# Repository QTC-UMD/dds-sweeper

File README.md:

# dds-sweeper

Raspberry Pi Pico interface for the AD9959 DDS.

If you use this project, please cite as:

E. Huegler, J. C. Hill, and D. H. Meyer, An agile radio-frequency source using internal sweeps of a direct digital synthesizer,
*Review of Scientific Instruments*, **94**, 094705 (2023)
[https://doi.org/10.1063/5.0163342](https://doi.org/10.1063/5.0163342)

## Specs

- The timing capabilities of the DDS-Sweeper are tied to the number of clock cycles the pico takes to send the next instruction.  

| Table Mode      | 1 Channel | 2 Channel | 3 Channel | 4 Channel |
|-----------------|-----------|-----------|-----------|-----------|
| Single Stepping | 500       | 750       | 1000      | 1250      |
| Sweep Mode      | 1000      | 1500      | 2000      | 2500      |

- At the default Pico Clock frequency of 125 MHz those clock cycle counts correspond to the following times:  

| Table Mode      | 1 Channel | 2 Channel  | 3 Channel  | 4 Channel  |
|-----------------|-----------|------------|------------|------------|
| Single Stepping | 4 $\mu s$ | 6  $\mu s$ | 8  $\mu s$ | 10 $\mu s$ |
| Sweep Mode      | 8 $\mu s$ | 12 $\mu s$ | 16 $\mu s$ | 20 $\mu s$ |

- The number of instructions you can store in the table depends on the type of sweep being performed, the number of channels being used, and the pico chip version. We allocated a maximum ram size of:

244 kB (RP 2040):

| Table Mode                  | 1 Channel | 2 Channel | 3 Channel | 4 Channel |
|-----------------------------|-----------|-----------|-----------|-----------|
| Single Stepping (Ext Timer) | 16656     | 8615      | 5810      | 4383      |
| Sweep Mode (Ext Timer)      | 8614      | 4382      | 2938      | 2210      |
| Single Stepping (Int Timer) | 5000      | 5000      | 5000      | 4032      |
| Sweep Mode (Int Timer)      | 5000      | 4032      | 2703      | 2033      |

500 kB (RP 2350):

| Table Mode                  | 1 Channel | 2 Channel | 3 Channel | 4 Channel |
|-----------------------------|-----------|-----------|-----------|-----------|
| Single Stepping (Ext Timer) | 34132     | 17654     | 11905     | 8981      |
| Sweep Mode (Ext Timer)      | 17654     | 8981      | 6022      | 4529      |
| Single Stepping (Int Timer) | 5000      | 5000      | 5000      | 5000      |
| Sweep Mode (Int Timer)      | 5000      | 5000      | 5000      | 4353      |

## How to flash the firmware

Download the latest [dds-sweeper.uf2 file](https://github.com/QTC-UMD/dds-sweeper/releases/latest/download/dds-sweeper.uf2).
On your Raspberry Pi Pico, hold down the "bootsel" button while plugging the Pico into USB port on a PC (that must already be turned on).
The Pico should mount as a mass storage device (if it doesn't, try again or consult the Pico documentation).
Drag and drop the `.uf2` file into the mounted mass storage device.
The mass storage device should unmount after the copy completes. Your Pico is now running the DDS Sweeper firmware!

## Usage

### Setup

When the DDS Sweeper is started, configuration is required before it can be used. It is often good to begin with a `reset` command, which resets the AD9959.

First, the clock should be setup with the `setclock` command, followed by the `setmult` command.

Second, the number of channels should be configured with the `setchannels` command.

Finally, the mode and timing should be setup with the `mode` command. The DDS Sweeper uses either discrete amplitude, frequency, and phase steps or sweeps of one parameter (possibly with steps of the other parameter) as its primitive instructions. The DDS Sweeper can then use internal timing (in which case it generates triggers internally after each step or sweep) or external timing (in which case it waits for external triggers).

### Program loading

Once setup is complete, instructions (steps or sweeps, depending on the mode) and timings can be loaded using the `set`, `seti`, or `setb` commands. In addition to output instructions, there are special stop and repeat instructions (which can only be loaded using `seti` and `setb`). With instructions are loaded, the address (order in which they are executed) is specified, so the order of loading need not match the order of execution. Timing is set per address, so it is common to all channels. The stop instruction ends program execution, while the repeat instruction restarts program execution from the beginning. Instructions are loaded into an uninitialized array, so skipping instruction addresses or failing to specify stop/repeat at the end of the program may result in undefined behavior.

### Execution

Finally, the program can be executed using the `start` or `hwstart` commands. If termination of the program is required before it reaches a `stop` command, the `abort` command can be used.

## DDS Units

- Output Amplitude is dependent on frequency (some people on Analog Devices forum mentioned amplitude and frequency are related by a sinc function)

- The frequency resolution of the AD9959 is $= \frac{f_{sys clk}}{2^{32}}$. At the default system clock of 500 MHz, the frequency resolution is $\approx 0.1164$ Hz. Frequency input to the DDS Sweeper using the `set` command will be rounded to an integer multiple of the frequency resolution. Frequency input to the DDS Sweeper using the `seti` or `setb` commands will be in units of the frequency resolution.

- The phase resolution of the AD9959 is $= \frac{360^\circ}{2^{14}} \approx 0.02197^\circ$. Phase offsets given using the `set` command will be rounded to a multiple of this resolution. Phase offsets given using the `seti` or `setb` commands will be in units of this resolution.

- The amplitude resolution of the AD9959 is $= \frac{1}{2^{10}} \approx 0.09767\%$. Amplitude scale factors given using the `set` command will be rounded to a multiple of this resolution. Amplitude scale factors given using the `seti` or `setb` commands will be in units of this resolution.

- When the DDS Sweeper uses internal timing to execute instructions, that time is based on the number of clock cycles of the Pico's system clock (which defaults to 125 MHz for an 8 ns period). Timing inputs using the `set` command are given in seconds and will be rounded to an integer multiple of the Pico system clock period. Timing input using the `seti` or `setb` commands is defined to be in units of the Pico system clock period.

## Sweeps

- Setting up a sweep:  
  
Sweeps are defined by two parameters, sweep delta and ramp rate.
- Sweep Delta defines the change in output amplitude/frequency/phase on each sweep step
- Ramp rate defines how often a sweep step is taken. It is based off of the AD9959's sync clock signal which will be one quarter of the AD9959's system clock. The ramp rate parameter specifies the number of sync clock cycles per sweep step. A ramp rate of 1 will cause the sweep delta to be applied every 1 sync clock cycle. For upward sweeps, the ramp rate parameter can have a value of 1-255. For downward sweeps the ramp rate can only be 1.  

For more details on sweeps, see [sweep details](SWEEP_DETAILS.md).

## Serial API

Note: Commands must be terminated with `\n`.

### Status commands

- `version`:  
Responds with a string containing the firmware version.

- `status`:  
Returns the operating status of the DDS-Sweeper.

  - `0`: manual mode
  - `1`: transitioning to buffered execution
  - `2`: buffered execution
  - `3`: aborting buffered execution
  - `4`: last buffered execution was aborted
  - `5`: transitioning to manual mode

- `clkstatus`:
Returns the clocking status of the DDS-Sweeper as three numbers: `<int:mode> <double:freq> <int:mult>`.
Mode can be `0` for internal clocking or `1` for external clocking of the AD9959.
The frequency is the AD9959 reference frequency, in Hz.
`mult` is the AD9959 PLL multiplier. The corresponding system frequency is `freq*-*mult`.

- `board`:
Responds with which type of board the firmware is running on: `pico1` or `pico2`.

- `getfreqs`:  
Responds with a multi-line string containing the current operating frequencies of various clocks (you will be most interested in `pll_sys` and `clk_sys`). Multiline string ends with `ok\n`.

### State commands

- `start`:  
Starts buffered execution immediately.

- `hwstart`:  
Starts buffered execution once an external trigger is received.

- `abort`:  
Stops buffered execution immediately.

### Setup commands

- `setclock <mode:int> <freq:int> (<pll_mult:int>)`:  
Reconfigures the source/reference clock.
  - Mode `0`: Use pico system clock as reference to the AD9959.
    In this mode, the frequency provided also sets the pico system clock
    and it cannot exceed 133 MHz.
    The dds sweeper defaults to this mode with a frequency of 125 MHz and a PLL multiplier of 4.
  - Mode `1`: Sets the AD9959 to receive a reference clock not from the pico.
    Setting this mode does not change the pico system clock.

  `pll_mult` is an optional input that sets the AD9959's PLL multiplier on the Reference Clock input. The default value is 4, giving the AD9959 a system clock of 500 MHz with the pico's 125 MHz reference. Valid values are 1 or 4-20.  
  The AD9959's PLL has an output range of 100-160 MHz or 255-500 MHz with VCO gain enabled. The pico will automatically enable the VCO gain bit if the requested frequency is in the upper range. If trying to use the PLL multiplier to generate a frequency between 160 and 255 MHz, there is no guarantee of operation.

- `setchannels <num:int>`:  
Sets how many channels being used by the table mode. Uses the lowest channels first, starting with channel 0. If number of channels is set to `0`, buffered execution instructions will be written to all 4 channels simultaneously.

- `mode <sweep-type:int> <trigger-source:int>`:  
Configures what mode the DDS-Sweeper is operating in
  - 0: single stepping / manual mode
  - 1: amplitude sweep
  - 2: frequency sweep
  - 3: phase sweep
  - 4: amplitude sweep with frequency/phase steps
  - 5: frequency sweep with amplitude/phase steps
  - 6: phase sweep with frequency/amplitude steps  

  The operating mode must be set before buffered execution instructions can be programmed into the DDS-Sweeper.  
  A `trigger-source` of `0` means the Sweeper is expecting external triggers. A `trigger-source` of `1` means the Sweeper will send its own triggers and `set` commands will require an additional `time` argument.

### Manual output commands

- `setfreq <channel:int> <frequency:float>`:  
Manually set the output frequency of a specified channel. Channels are 0-3 and frequencies are in Hz. If `debug` is set to on, it will respond with the actual frequency set. The Sweeper must be in manual mode.

- `setphase <channel:int> <phase_offset:float>`:  
Manually set the phase offset of a specified channel. Channels are 0-3 and offsets are in degrees. If `debug` is set to on, it will respond with the actual degree offset set. The Sweeper must be in manual mode.

- `setamp <channel:int> <amplitude_scale_factor:float>`:  
Manually set the amplitude scale factor of a specified channel. Channels are 0-3 and amplitude scale factors are a precentage of the maximum output voltage. If `debug` is set to on, it will respond with the actual frequency set. The Sweeper must be in manual mode.

### Data loading commands

- `set`:  
Sets the value of instruction number `addr` for channel `channel` (zero indexed). `addr` starts at 0. It looks different depending on what mode the sweeper is in. If `Debug` is set to `on` it will respond with the actual values set for that instruction.
  - Single Stepping (mode 0): `set <channel:int> <addr:int> <frequency:float> <amplitude:float> <phase:float> (<time:float>)`
  - Sweep Mode (modes 1-3): `set <channel:int> <addr:int> <start_point:float> <end_point:float> <sweep_rate:float> (<time:float>)`

    `start_point` is the value the sweep should start from, and `end_point` is where it will stop. `sweep_rate` is the amount that the output should change in each quantity's units per second (further info below). In the AD9959, the sweep clock runs at one quarter the system clock. The types of values expected for `start_point`, `end_point`, and `sweep_rate` are different depending on the type of sweep:  
    - Amplitude Sweeps (mode 1)  
      `start_point` and `end_point` should be decimals between 0 and 1 that represent the desired proportion of the maximum output amplitude. `sweep_rate` is then that proportion per second. The resolution of the start and end values is $\frac{1}{1024} \approx 0.09766$.
    - Frequency Sweeps (mode 2)  
      `start_point` and `end_point` are frequencies in Hz, with `sweep_rate` in Hz per second. The start and end points can have decimal values, but they will be rounded to the nearest multiple of the frequency resolution ($\frac{f_{sysclk}}{2^{32}}$).
    - Phase Sweeps (mode 3)
      `start_point`, `end_point` are in degrees, with `sweep_rate` in degrees per second. The start and end points can have decimal values, but they will be rounded to the nearest multiple of the phase resolution ($\frac{360^\circ}{2^{14}} \approx 0.02197^\circ$).

  - Sweep and Single Stepping Mode (modes 4-6): `set <channel:int> <addr:int> <start_point:float> <end_point:float> <sweep_rate:float> <secondary1:double> <secondary2:double> (<time:float>)`

  These modes perform a linear sweep on one of the parameters, while simultaneously single stepping on the other two parameters.
  - Amplitude Sweeps (mode 4)  
    `secondary1` is the frequency, and `secondary2` is the phase offset.
  - Frequency Sweeps (mode 5)  
    `secondary1` is the amplitude scale factor, and `secondary2` is the phase offset.
  - Phase Sweeps (mode 6)  
    `secondary1` is the frequency, and `secondary2` is the amplitude scale factor.

- `seti`:  
Sets the value of instruction number `addr` for channel `channel` (zero indexed). `addr` starts at 0. It looks different depending on what mode the sweeper is in. If `Debug` is set to `on` it will respond with the actual values set for that instruction. `seti` uses integer values (AD9959 units) rather than floating point values. Otherwise, it is the same as `set`.
  - Single Stepping (mode 0): `seti <channel:int> <addr:int> <frequency:int> <amplitude:int> <phase:int> (<time:int>)`
  - Sweep Mode (modes 1-3): `seti <channel:int> <addr:int> <start_point:int> <end_point:int> <delta:int> <ramp-rate:int> (<time:int>)`

    `start_point` is the value the sweep should start from, and `end_point` is where it will stop. `delta` is the amount that the output should change by every cycle of the sweep clock. In the AD9959, the sweep clock runs at one quarter the system clock. `ramp-rate` is an additional divider that can applied to slow down the sweep clock further, must be in the range 1-255. The types of values expected for `start_point`, `end_point`, and `delta` different depending on the type of sweep  
    - Amplitude Sweeps (mode 1)  
      `start_point` and `end_point` should be integers between 0 and 1023 (inclusive).
    - Frequency Sweeps (mode 2)  
      `start_point`, `end_point`, and `delta` are integers between 0 and $2^{32} - 1$ in units of system clock rate (typically $500$ MHz) over $2^{32}$.
    - Phase Sweeps (mode 3)
      `start_point`, `end_point`, and `delta` are between 0 and 65535 (inclusive).

  - Sweep and Single Stepping Mode (modes 4-6): `set <channel:int> <addr:int> <start_point:int> <end_point:int> <delta:int> <ramp-rate:int> <secondary1:int> <secondary2:int> (<time:int>)`

    These modes perform a linear sweep on one of the parameters, while simultaneously single stepping on the other two parameters.
    - Amplitude Sweeps (mode 4)  
      `secondary1` is the frequency, and `secondary2` is the phase offset.
    - Frequency Sweeps (mode 5)  
      `secondary1` is the amplitude scale factor, and `secondary2` is the phase offset.
    - Phase Sweeps (mode 6)  
      `secondary1` is the frequency, and `secondary2` is the amplitude scale factor.

- `setb <start address:int> <instruction count:int>`:  
Bulk setting of instructions in binary. `start address` is the address of the first instruction loaded. `instruction count` instructions will be programmed. If there is not sufficient space for that many instructions, the response will be an error message. Otherwise, the response will be `ready for <byte count:int> bytes`, where `byte count` is the number of bytes the device is expecting. An array of instructions can then be transmitted. Note that all active channels are loaded together. The layout of the instruction array is mode dependent, and in the table below each mode is assumed to use external timing (where internal timing bytes are in parentheses and the dtype list must have `, ('time', '<u4')` appended)

| Mode  | Bytes per channel per instruction  | np.dtype  |
|---| :---: |:---:|
| Single Stepping (mode 0)  | 8 (12) | `[('frequency', '<u4'), ('amplitude', '<u2'), ('phase', '<u2')]`  |
| Amplitude Sweeps (mode 1)  | 7 (11) |  `[('start_amplitude', '<u2'), ('stop_amplitude', '<u2'), ('delta', '<u2'), ('rate', '<u1')]` |
| Frequency Sweeps (mode 2) | 13 (17) |  `[('start_frequency', '<u4'), ('stop_frequency', '<u4'), ('delta', '<u4'), ('rate', '<u1')]` |
| Phase Sweeps (mode 3)  | 7 (11) | `[('start_phase', '<u2'), ('stop_phase', '<u2'), ('delta', '<u2'), ('rate', '<u1')]` |
| Amplitude Sweep and Single Stepping (mode 4) | 13 (17)  | `[('start_amplitude', '<u2'), ('stop_amplitude', '<u2'), ('delta', '<u2'), ('rate', '<u1'), ('frequency', '<u4'), ('phase', '<u2')]`  |
| Frequency Sweep and Single Stepping (mode 5) | 17 (21) | `[('start_frequency', '<u4'), ('stop_frequency', '<u4'), ('delta', '<u4'), ('rate', '<u1'), ('amplitude', '<u2'), ('phase', '<u2')]`  |
| Phase Sweep and Single Stepping (mode 6)  | 13 (17) | `[('start_phase', '<u2'), ('stop_phase', '<u2'), ('delta', '<u2'), ('rate', '<u1'), ('frequency', '<u4'), ('amplitude', '<u2')]`  |

### Flash commands

- `save`:  
Saves the buffered execution table to nonvolatile memory so that it can be recovered later (after a power cycle).

- `load`:  
Retrieves the buffered execution table stored in nonvolatile memory and restores it to system memory so that it can be run. A saved table must be loaded before it can be run.

### Debugging commands

- `debug <state:str>`:  
Turns on extra debug messages printed over serial. `state` should be `on` or `off` (no string quotes required). On by default.

- `numtriggers`:  
Responds with the number of triggers processed since the last call of `start`

- `program`:  
Reboots the Pi Pico into firmware flashing mode. Serial will immediately disconnect and a mass storage device should appear.

## Compiling the firmware

If you want to make changes to the firmware, or want to compile it yourself (because you don't trust binary blobs from the internet), we provide a docker configuration to help you do that.

1. Install docker desktop and make sure it is running (if you are on Windows, you may have to mess around a bit to get virtualisation working at an operating system level)
2. Clone this repository
3. Open a terminal with the current working directory set to the repository root (the `docker-compose.yaml`` file should be there)
4. Run `docker compose build --pull` to build the docker container
5. Run `docker compose up` to build the PrawnBlaster firmware.

Step 4 will take a while as it has to build the docker container.
If it is slow to download packages from the Ubuntu package repositories, consider providing an explicit apt mirror that is fast for you: `docker compose build --pull --build-arg APT_MIRROR="http://azure.archive.ubuntu.com/ubuntu/"`.

If you want to change which version of the pico SDK it builds against, this is set in the `build/docker/Dockerfile` file.
Just change the git tag of the pico SDK that gets cloned out by git, then rebuild the docker container (see step 4).

Note once the docker container is built, you can run step 5 as many times as you like.
You do not need to rebuild the container, even if you make changes to the PrawnBlaster source code.
You only need to rebuild the docker container if you modify the `build/docker/Dockerfile` file.

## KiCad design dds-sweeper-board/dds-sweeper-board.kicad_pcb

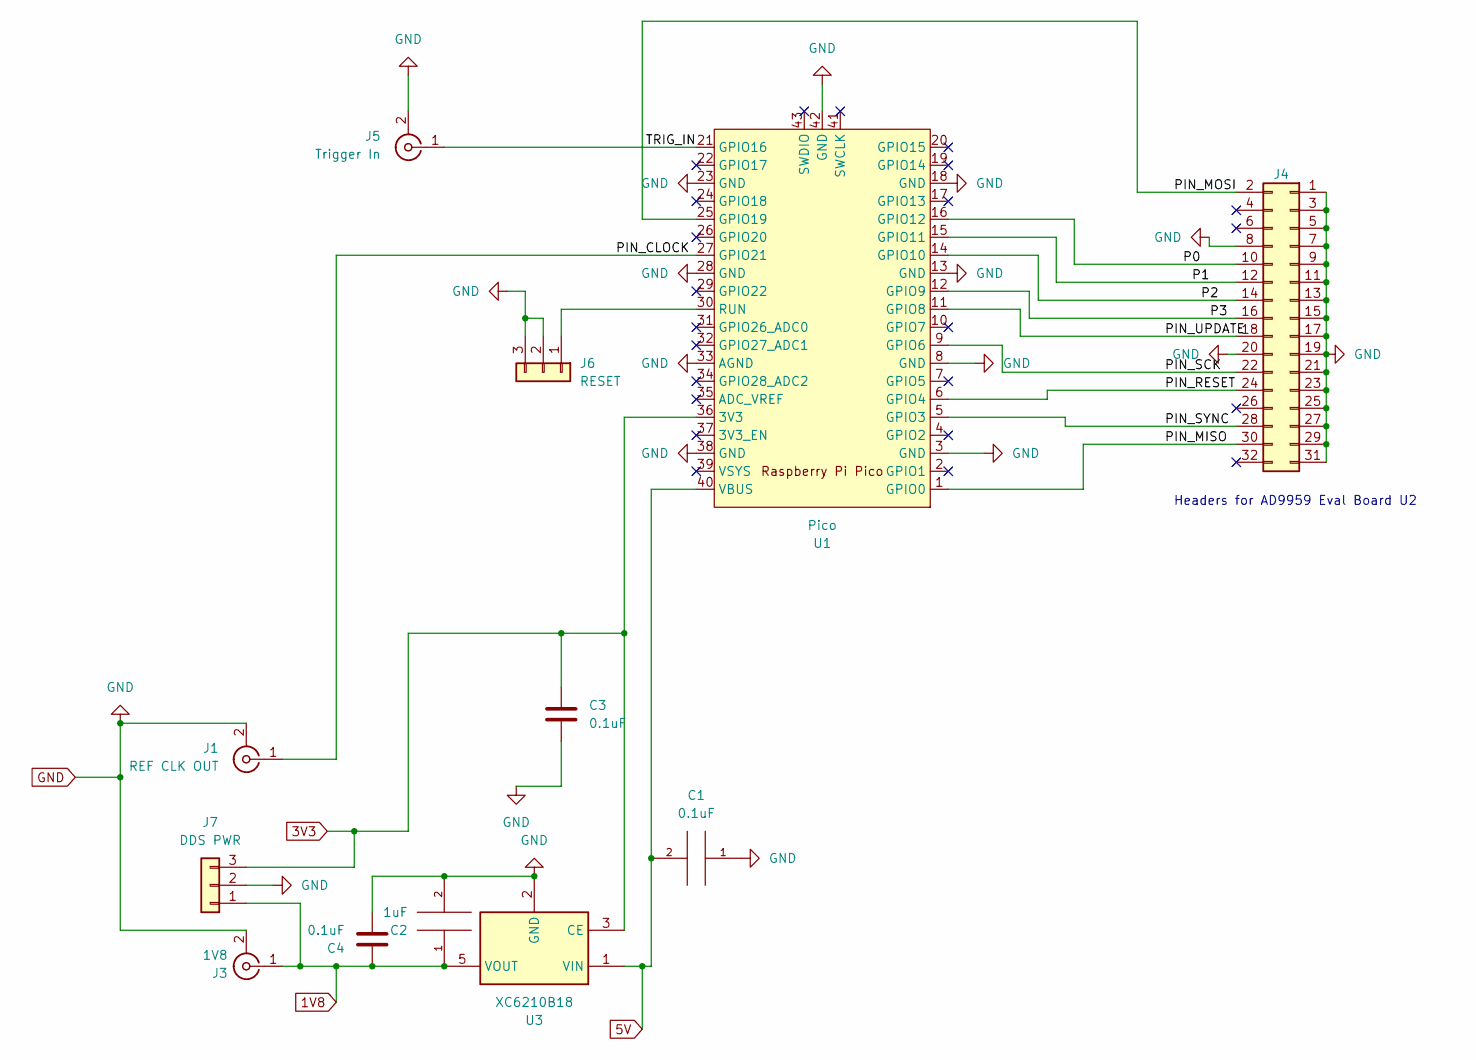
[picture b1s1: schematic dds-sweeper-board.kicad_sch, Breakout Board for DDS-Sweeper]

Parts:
C1, C3, C4: 0.1uF; C_0805_2012Metric_Pad1.18x1.45mm_HandSolder
C2: 1uF; C_0805_2012Metric_Pad1.18x1.45mm_HandSolder
J1: REF CLK OUT; SMA_Samtec_SMA-J-P-X-ST-EM1_EdgeMount
J3: 1V8; SMA_Samtec_SMA-J-P-X-ST-EM1_EdgeMount
J4: AD9959 Eval Header; PinSocket_2x16_P2.54mm_Vertical
J5: Trigger In; SMA_Samtec_SMA-J-P-X-ST-EM1_EdgeMount
J6: RESET; PinSocket_1x03_P2.54mm_Vertical
J7: DDS PWR; PinSocket_1x03_P2.54mm_Vertical
U1: Pico; RPi_Pico_SMD
U3: XC6210B18; SOT-23-5

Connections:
1V8: C2.1, C4.1, J3.1 (In), J7.1, U3.5 (VOUT)
3V3: C3.2, J7.3, U1.36 (3V3), U3.3 (CE)
5V: C1.2, U1.40 (VBUS), U3.1 (VIN)
/P0: J4.10, U1.16 (GPIO12)
/P1: J4.12, U1.15 (GPIO11)
/P2: J4.14, U1.14 (GPIO10)
/P3: J4.16, U1.12 (GPIO9)
/PIN_CLOCK: J1.1 (In), U1.27 (GPIO21)
/PIN_MISO: J4.30, U1.1 (GPIO0)
/PIN_MOSI: J4.2, U1.25 (GPIO19)
/PIN_RESET: J4.24, U1.6 (GPIO4)
/PIN_SCK: J4.22, U1.9 (GPIO6)
/PIN_SYNC: J4.28, U1.5 (GPIO3)
/PIN_UPDATE: J4.18, U1.11 (GPIO8)
/TRIG_IN: J5.1 (In), U1.21 (GPIO16)
GND: C1.1, C2.2, C3.1, C4.2, J1.2 (Ext), J3.2 (Ext), J4.1, J4.3, J4.5, J4.7, J4.8, J4.9, J4.11, J4.13, J4.15, J4.17, J4.19, J4.20, J4.21, J4.23, J4.25, J4.27, J4.29, J4.31, J5.2 (Ext), J6.2, J6.3, J7.2, U1.3 (GND), U1.8 (GND), U1.13 (GND), U1.18 (GND), U1.23 (GND), U1.28 (GND), U1.33 (AGND), U1.38 (GND), U1.42 (GND), U3.2 (GND)
unnamed: J6.1, U1.30 (RUN)

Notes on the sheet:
Headers for AD9959 Eval Board U2

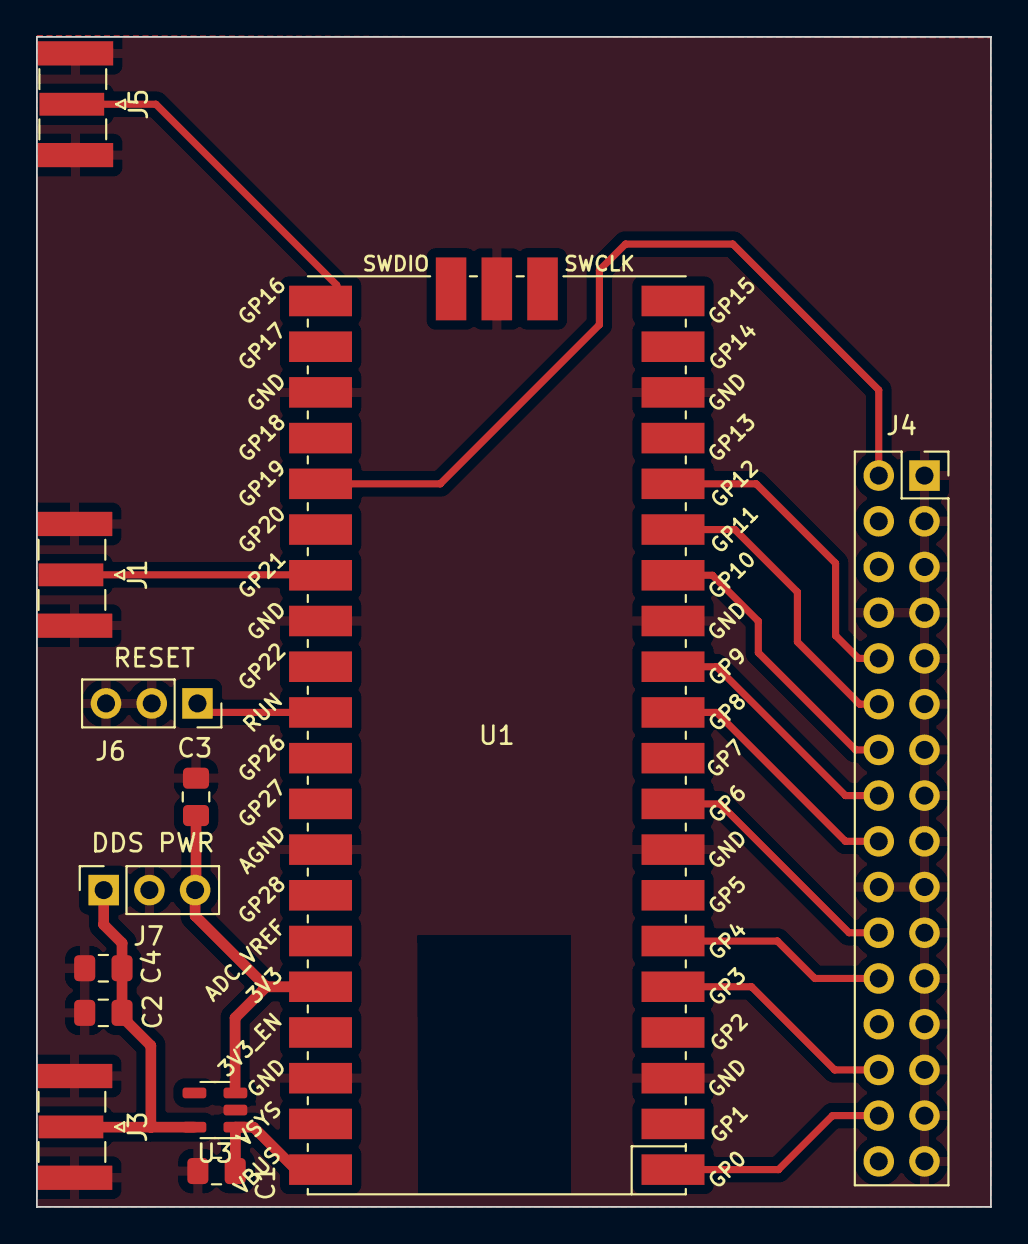
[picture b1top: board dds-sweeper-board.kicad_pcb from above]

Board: 2 copper layers, 53.0 x 65.0 mm, 12 parts (0 on the bottom side), 17 nets.

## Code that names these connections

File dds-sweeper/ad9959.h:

#ifndef _AD9959_H
#define _AD9959_H

#include <math.h>
#include <stdio.h>
#include <string.h>

#include "hardware/clocks.h"
#include "hardware/spi.h"
#include "hardware/structs/watchdog.h"
#include "pico/stdlib.h"

// Default Pins to use
#define PIN_MISO 0  //RX
#define PIN_MOSI 19  //TX
#define PIN_SCK 6
#define PIN_SYNC 3
#define PIN_CLOCK 21
#define PIN_UPDATE 8
#define PIN_RESET 4
#define P0 12
#define P1 11
#define P2 10
#define P3 9
#define PROFILE_ASC false
#define TRIGGER 16
#define INT_TRIGGER 17

#define PIO_TRIG pio0
#define PIO_TIME pio1

#define SPI spi0

// AD9959 registers
#define AD9959_REG_CSR 0x00
#define AD9959_REG_FR1 0x01
#define AD9959_REG_FR2 0x02
#define AD9959_REG_CFR 0x03
#define AD9959_REG_FTW 0x04
#define AD9959_REG_POW 0x05
#define AD9959_REG_ACR 0x06
#define AD9959_REG_LSRR 0x07
#define AD9959_REG_RDW 0x08
#define AD9959_REG_FDW 0x09
#define AD9959_REG_CW 0x0A

// Instruction memory maps
// Defines offset in instruction array where register address is stored
// Register value starts at offset of address
#define INS_CSR 0
// For Single Step
#define INS_SS_FTW 2
#define INS_SS_POW 7
#define INS_SS_ACR 10
// For AMP/AMP2 sweep
#define INS_AMP_ACR 2
#define INS_AMP_LSRR 6
#define INS_AMP_RDW 9
#define INS_AMP_FDW 14
#define INS_AMP_CW 19
#define INS_AMP_CFR 24
#define INS_AMP_FTW 28
#define INS_AMP_POW 33
// For FREQ/FREQ2 sweep
#define INS_FREQ_FTW 2
#define INS_FREQ_LSRR 7
#define INS_FREQ_RDW 10
#define INS_FREQ_FDW 15
#define INS_FREQ_CW 20
#define INS_FREQ_CFR 25
#define INS_FREQ_ACR 29
#define INS_FREQ_POW 33
// For PHASE/PHASE2 sweep
#define INS_PHASE_POW 2
#define INS_PHASE_LSRR 5
#define INS_PHASE_RDW 8
#define INS_PHASE_FDW 13
#define INS_PHASE_CW 18
#define INS_PHASE_CFR 23
#define INS_PHASE_FTW 27
#define INS_PHASE_ACR 32

typedef struct ad9959_config {
    double ref_clk;
    uint32_t pll_mult;
    int sweep_type;
    uint channels;
    uint mirror;
} ad9959_config;

// get tuning words
double get_asf(double amp, uint16_t* asf);
double get_ftw(ad9959_config* c, double freq, uint32_t* ftw);
double get_pow(double phase, uint16_t* pow);
double get_time(ad9959_config* c, double time, uint32_t* cycles);

void load_acr(uint16_t asf, uint8_t* buf);
void load_ftw(uint32_t ftw, uint8_t* buf);
void load_pow(uint16_t pow, uint8_t* buf);

// send tuning words
void send_channel(uint8_t reg, uint8_t channel, uint8_t* buf, size_t len);
void send(uint8_t reg, uint8_t* buf, size_t len);

// Readback from AD9959
void read_reg(uint8_t reg, size_t len, uint8_t* buf);
void read_all();

// control
void set_pll_mult(ad9959_config* c, uint mult);
void set_ref_clk(ad9959_config* c, uint64_t freq);
void single_step_mode();
void clear();

// Sweep rate algorithm
double approx_double_32(double f, uint32_t * numerator, uint * denominator, uint32_t p_max, uint32_t q_max);
double approx_double_16(double f, uint16_t * numerator, uint * denominator, uint16_t p_max, uint16_t q_max);

#endif

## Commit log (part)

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2022-06-15 updated git ignore
2022-06-15 added project files
2022-06-16 added basic frequency sweeping
2022-06-16 fixed frequency sweep issue
2022-06-21 pico sys-clk works as ref-clk
2022-06-21 multiple sweeps up and down working
2022-06-24 pio, triggering, multithreaded
2022-06-24 removed unnecessary lines
2022-06-27 basic serial communication
2022-06-28 increase clock for spi transfers
2022-06-28 fixed first read error
2022-06-28 some more serial commands
2022-06-29 set single tone frequency
2022-06-29 fixed setfreq
2022-06-29 added documentation
2022-06-29 enable uart
2022-06-30 read all registers over serial
2022-07-05 changed how down sweeps are triggered
2022-07-05 remote programming support
2022-07-05 add status guards
2022-07-05 fixed
2022-07-05 user specifiable amplitudes -broken
2022-07-06 fixed falling sweep rate
2022-07-06 autoclear is source of issue
2022-07-06 bug with amplitude sweeps
2022-07-07 allow changing down sweep rates
2022-07-07 more documentation
2022-07-07 fallback
2022-07-07 corrections
2022-07-07 setamp command
2022-07-08 setclock command
2022-07-08 single tone mode
2022-07-08 updated todo list
2022-07-08 moved to issues
2022-07-12 profile pin masking
2022-07-12 setchannels command
2022-07-13 when using only one channel all of the channels will output the same
2022-07-13 changed order of channels in memory
2022-07-13 fixed off by one error when using more than 2 channels
2022-07-14 external clock mode added
2022-07-15 ability to specify times when programming instructions
2022-07-15 eliminated downtime between timed sweeps
2022-07-15 set_phase command looks correct
2022-07-18 code clean up
2022-07-18 single step on phase freq and amp all at once
2022-07-18 use pio interupts to trigger spi instead of waits
2022-07-18 changed stop instruction
2022-07-18 updated docs
2022-07-19 fixed loopback for all modes
2022-07-20 better response workaround
2022-07-20 made ad9959 config system less complicated
2022-07-20 fixed documentation and error messages
2022-07-20 added save and load to readme
2022-07-20 runs the table from flash using dma
2022-07-21 correctly save to RAMand play back
2022-07-21 reduce number of flash writes
2022-07-22 fix timer number of instructions and memory check
2022-07-22 clean up and commented code
2022-07-25 added attributions for prawnblaster/pineblaster code
2022-07-26 updated documentation
2022-07-27 found a similar arduino project
2022-07-28 added setamp
2022-07-28 fixed broken repeat mode
2022-07-28 changed internally timed mode to be compatible with repeat mode
2023-01-09 removed debug printing
2023-01-11 tidy code
2023-01-11 added sweep setup info
2023-01-17 clear sweep accumulator before downward sweeps as well
2023-01-17 added info on timing and updated notes
2023-01-17 removed unnecessary info and old bugs that have been fixed
2023-01-17 move images
2023-01-17 tested removing responses to speed up communication
2023-01-17 board updates
2023-01-17 added hwstart functionality
2023-01-17 added backups to gitignore
2023-01-17 removed backups from repo
2023-01-18 updated board desings
2023-01-18 only track gerber files for the board design
2023-01-19 added trigger input
2023-01-23 readregs turns off sweep mode - fixes #31
2023-01-23 removed variability in when pico starts sending SPI data
2023-01-24 fixed print debug statements
2023-01-24 edit documentation and add pictures of sweep modes
2023-01-25 added firmware file
2023-01-25 added flash instructions
2023-01-25 added testing file
2023-01-25 updated board files
2023-01-27 made hwstart go on first trigger, not send a fake one
2023-01-27 redo hwstart so it actually starts on time and fix abort command
2023-01-27 fixed phase sweep rate being set incorrectly
2023-01-27 removed extra figures
2023-01-27 removed debugging info
2023-01-27 cleaned up tests
2023-02-01 updated version number
2023-02-01 fixed pictures
2023-02-01 fixed tables not formatting correctly
2023-02-08 added last printed files
2023-02-24 fixed picture links
2023-02-24 use img tags for images in notebook
2023-02-24 add image alt text
2023-02-24 added full kicad project
2023-02-27 stop autoclearing phase accumulator in single stepping mode
2023-02-27 fixed version mismatch and added type hints/comments
2023-03-03 increased trace width and spacing
2023-03-03 fixed board traces and keep outs
2023-03-08 removed hard coded trigger pin from pio instructinos
2023-03-10 Create LICENSE
2023-03-10 added sweep pattern for paper data
2023-03-10 updated sawishtooth script
2023-03-15 added functionality for setting secondary params during a sweep
2023-03-31 added functionality for single stepping secondary parameters
2023-04-07 improved recoverability from fatal error
2023-04-07 hit reset pin on software reset
2023-04-19 bigger traces
2023-04-19 turned off input buffer on trigger pin
2023-04-21 added a comment
2023-08-22 Unzip KiCAD project, track individual files.
    Also updates project to KiCAD 7.0, made some minor tweaks to layout
    and schematic.
2024-03-19 Update cmake build directory to point to new name
2024-03-19 Add docker files for building the firmware
2024-03-19 Add github workflow to get automatic builds.
2024-03-19 Update the readme to reflect the new firmware building.
2024-03-19 Put workflow in correct folder.
2024-03-19 Fix errors in workflow.
2024-09-24 Implement faster serial from the prawn projects.
2024-10-07 Fix remaining `printf` in ad9959.c
2024-10-07 Update testing notebook to actually run with current firmware (ie return strings only have `\n` now, not `\r\n`)
2024-10-08 Bump minor version
2024-10-08 Separate github release workflow from build
    This ensures github token write permissions are limited to part of
    workflow that actually needs it.
    Change also prevents github release from running on forks.
2024-10-09 Fix logic for checking if PLL multiplication factor is valid
2024-10-11 Fix upload of release assets in workflow
2024-10-11 Ensure release gets auto-generated release notes
2024-10-11 Modify firmware to use new pins
2024-10-13 Fixes to external triggering
2024-10-14 Need to reinitialize PIO after mode change. Typo fix in timer.
2024-11-03 Fixed typo in comments/error messages
2024-11-10 Start refactoring set_ins so we can have floating point and integer modes
2024-11-11 Split set_ins into functions for each mode, with separate integer and double functions
2024-11-11 Binary transfers working for single step mode
2024-11-12 Added binary transfers for sweep modes (untested)
2024-12-08 Moved buffer decoding code into functions to reduce duplication
2024-12-08 Load timing
2025-01-07 Fix argument checking for single step set/seti. Reset serial input array before each command.
2025-01-08 Begin refactoring and expanding documentation.
2025-01-21 adding working tests for Phase sweeps, pure amplitude sweeps - Frequency sweeps of both types and amplitude mode 4 WIP
2025-01-22 adding some setters to scope class but also WIP
2025-01-24 cleanup of some tests / removing some fruitless commented out tests
2025-01-24 some typos in readme
2025-01-31 Fix step registers in mode 6.
2025-02-04 Correct errors in README and add confirmation return to command.
2025-02-07 Fix incorrect byte extraction from setb amplitude sweep loading. Removed extraneous print.
2025-02-07 Fix incorrect byte extraction from setb phase sweep loading.
2025-02-14 cleanup, a test on frequency sweeps, since this didn't go anywhere I'm going to write the readtable() func in firmware
2025-02-18 Merge `setclock` and `setmult` commands into a single `setclock` command.
    I've confirmed firmware builds, but haven't tested functionality yet.
2025-02-18 Simplify clk_status tracking since ad9959_config tracks most of the data already.
    Also removes mutex protection since reads/writes can't occur simultaneously.
2025-02-18 Attempt to allow specifying a single output channel.
    Modifies such that `setchannels 0` writes to all channels.
    `setchannels 1` will only enable channel 0.
    Note: this is likely to break the testing notebooks.
2025-02-18 final bit of notebook cleanup to move setb commands fully out of original notebook. set and seti remain in the original
2025-02-20 switching binary tests to class based approach for readability and similarity to labscript. beginning to test new setclock commands and channel mirroring
2025-02-21 I see the pow in the table! so I must have the pow offset right and everything else wrong
2025-02-24 I was overcomplicating, get_instructions() called from eadtable now spits out binary block with some python handling
2025-02-25 readtable is finished, getmode is nearly finished, just needs an output for when more than one channel is being used
2025-02-26 adding in some offsets since the raw byte output misses the end of instructions otherwise
2025-02-26 added some handling for the readtable byte blocks to put in a header and pipe separators, currently looks ugly but its to make debugging easier (potentially)
2025-02-27 get_memory_layout handles multiple channels, and logic to chunk response out since fast_serial_write has limit of 128
2025-02-28 Last commits before review, will write up summary for helping with diff unreadability
2025-03-07 changed classes to use CapWords convention and objects to use lowercase_with_underscores for PEP8 (and consistency)
2025-03-10 adding notebook with code for testing command
2025-03-11 cut down the function to be less memory hungry, favored fast_serial_printf over sprints for concats. This all works on this branch.
2025-03-12 removing dtypes in firmware, this will be handled in documentation
2025-03-12 switching setb docs to table
2025-03-12 removing old line from get_memory_layout and some janky wording in docs
2025-03-21 Initial framework for tracking the stop command.
    Commit contains debug print, has not replaced for-loop calcs,
    and does not protect against running tables without a stop yet.
2025-03-21 Fix readme typos
2025-03-21 Clean up superfluous debug prints.
    Debug now only reports rounding of settings.
2025-03-21 Update readme for new timing semantics
2025-03-21 Replace for-loop instruction number counting with cached value.
2025-03-21 Missing ;
2025-03-21 Fixed some linting issues in the markdown files
2025-03-21 Attempt to have errors in firmware build be properly caught in github action.
    Note: commit introduces intentional error to test this.
2025-03-21 typo from my old PEP8 fix, fixed inconsistent calls of Binary_Routines -> BinaryRoutines
2025-03-21 Confirm change doesn't trigger when code compiles correctly.
2025-03-21 Move global definition
2025-03-21 fix swap in multiply vs divide logic in get_time and used g format for float printing
2025-03-24 FROM/as case mismatch
2025-03-24 switch to camel case for correct function call
2025-03-25 swap internal and external timer order in README and add a hint
2025-03-28 saving tests and readme edits
2025-03-31 sentence balance
2025-04-03 removing extra comment and saving instruction tests
2025-04-03 potentially useful, unsure if it should make it to main
2025-04-04 adding the scaling factors before I forget them, will test tomorrow
2025-04-04 upwards sweeps calculate correctly, but are now in different units than the downwards, need to fix
2025-04-04 an idea, why not have the falling case just use the same function but enforce the denominator to be 1? I believe thats the same as before, but outskirts the bounds on get_asf()
2025-04-07 fixed asymmetry in amp sweeps (needed a slightly longer time) and cleanup on comments in dds-sweeper.c
2025-04-08 implementing changes
2025-04-08 carter caught ins_from_buffer being used instead of ins_count
2025-04-08 redoing instruction counts for 243 KB
2025-04-08 fixing clunkiness
2025-04-09 ensuring phase is within bounds
2025-04-09 forgot to delete those old helper function cells here too, deleted now.
2025-04-09 cleaned out individual tests, keeping general tests
2025-04-09 Bump minor version for release
2025-04-16 Bumpy SDK to v2.1.1
2025-04-16 Update workflow
2025-04-16 Drop previous docker exit code strategy since it fails with multiple build targets.
2025-04-17 Alternate check that explicitly checks the service exit codes, counts how many non-zero ones, and exits if the answer is not 0.
    Probably.
2025-04-17 Use proper docker compose command
2025-04-17 rp2040 244 kB and rp3050 500 kB instructions counted
2025-04-17 Document `board` command and change its response slightly.
